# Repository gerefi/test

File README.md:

<div align="center">

<b>GPL open-source ECU</b>

</div>

# gerEFI

See [gcc_version_check.c](https://github.com/gerefi/gerefi/blob/master/firmware/gcc_version_check.c) for recommended version of GCC.

Current binaries are always available on our [build server](http://gerefi.com/build_server/)

[shop.gerEFI.com](https://www.shop.gerefi.com/)

# Cloning the repository
`git clone https://github.com/gerefi/gerefi.git`
Important note - we now use submodules:

`git submodule update --init`

# What do we have here?
 * [Firmware](/firmware) Source code for open source engine control unit for stm32 chips incuding [implementation overview](https://github.com/gerefi/gerefi/blob/master/firmware/readme.md)
 * [Hardware](/hardware) KiCAD files for our older PCBs
 * [gerEFI console](/java_console) gerEFI own native tuning software
 * [Simulator](/simulator) win32 or posix version of firmware allows to explore without any hardware
 * [Unit Tests](/unit_tests) Unit tests of firmware pieces
 * [Misc tools](/java_tools) Misc development utilities
 * [Software Development process](misc/SoftwareDevelopmentProcess.md)

# External Links

 * [Forum](http://gerefi.com/forum)
 * [Documentation](https://github.com/gerefi/gerefi/wiki)
 * [Doxygen documentation](http://gerefi.com/docs/html)
 * [General source code Q&A](http://gerefi.com/forum/viewtopic.php?f=5&t=10)
 * [Facebook](https://www.facebook.com/gerEfiECU)
 * [YouTube](https://www.youtube.com/user/gerefi)
 * [Patreon](https://www.patreon.com/gerefi)

# Building the Code
Check out https://gerefi.com/forum/viewtopic.php?f=5&t=9

# Release Notes

See [the changelog](firmware/CHANGELOG.md)

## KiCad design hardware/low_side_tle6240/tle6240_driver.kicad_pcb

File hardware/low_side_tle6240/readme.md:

TLE6240GP module - integrated low side switch

https://youtu.be/H8Tr4kTaYAI

https://gerefi.com/forum/viewtopic.php?f=4&t=398

All 16 channels can be controlled via the serial interface (SPI). In addition to the serial control it is possible to
control channel 1 to 4 and 9 to 12 direct in parallel with a separate input pin.

https://github.com/gerefi/gerefi_documentation/blob/master/oem_docs/Infineon/Infineon-TLE6240GP-DS-v03_03-en.pdf

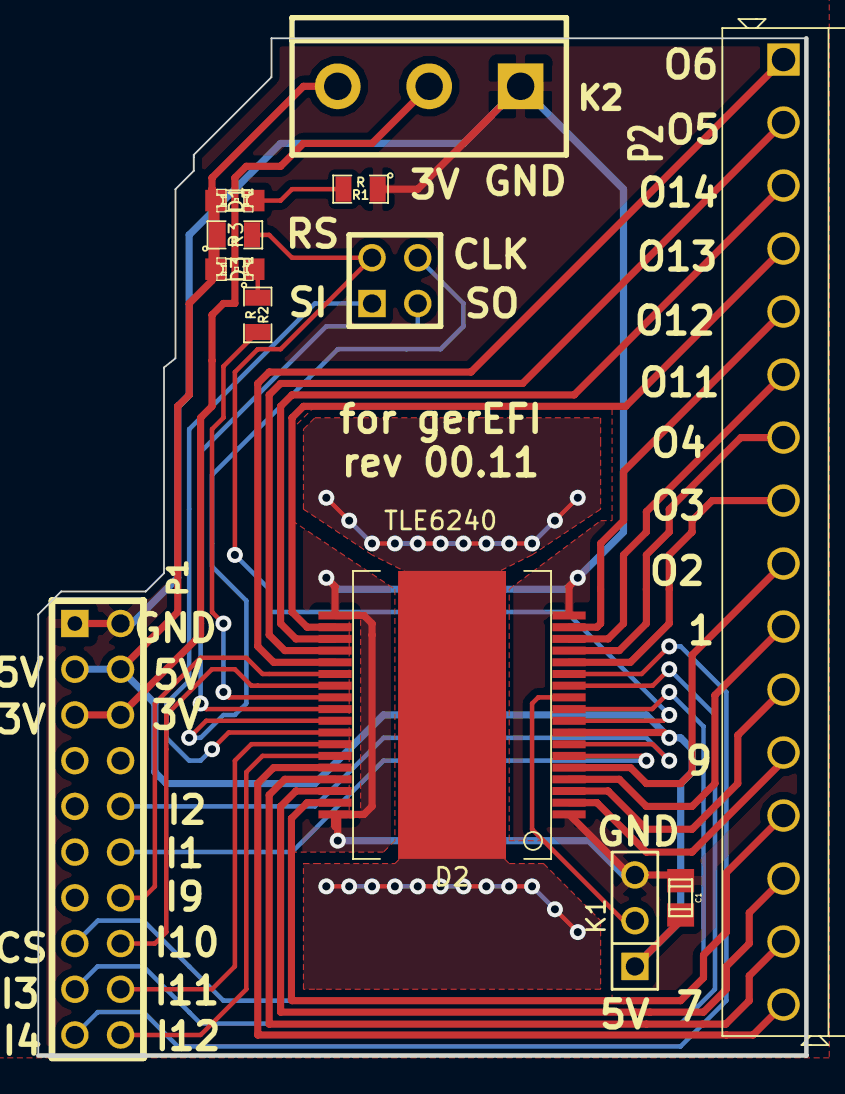
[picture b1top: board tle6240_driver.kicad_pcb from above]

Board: 2 copper layers, 42.7 x 56.5 mm, 12 parts (0 on the bottom side), 36 nets.

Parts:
C1: C; c_0805
D1, D3: LED; LED-0805
D2: TLE6240; PG-DSO-36
K1: JUMPER3; PIN_ARRAY_3X1
K2: CONN_3; bornier3
P1: CONN_10X2; PIN_ARRAY_10X2
P2: CONN_16; SIL-16_3.5MM
P3: CONN_2X2; PIN_ARRAY_2X2
R1, R2, R3: R; SM0805

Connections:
+5V: C1.1, D1.1, D2.8, D3.1, K1.1, K2.3, P1.3, P1.4, R3.1
/+3.3V: K2.2, P1.5, P1.6
/CS: D2.10, P1.15
/Fault: D2.26, R2.2
/IN1: D2.6, P1.12
/IN2: D2.7, P1.10
/IN3: D2.12, P1.17
/IN4: D2.13, P1.19
/IN9: D2.24, P1.14
/IN10: D2.25, P1.16
/IN11: D2.30, P1.18
/IN12: D2.31, P1.20
/OUT1: D2.4, P2.10
/OUT2: D2.5, P2.9
/OUT3: D2.14, P2.8
/OUT4: D2.15, P2.7
/OUT5: D2.22, P2.2
/OUT6: D2.23, P2.1
/OUT7: D2.32, P2.16
/OUT8: D2.33, P2.15
/OUT9: D2.2, P2.12
/OUT10: D2.3, P2.11
/OUT11: D2.16, P2.6
/OUT12: D2.17, P2.5
/OUT13: D2.20, P2.4
/OUT14: D2.21, P2.3
/OUT15: D2.34, P2.14
/OUT16: D2.35, P2.13
/PRG: D2.11, K1.2
/Reset: D2.9, P3.2, R3.2
/SCLK: D2.28, P3.4
/SI: D2.29, P3.1
/SO: D2.27, P3.3
GND: C1.2, D2.1, D2.18, D2.19, D2.36, K1.3, K2.1, P1.1, P1.2, R1.1
unnamed: D3.2, R2.1
unnamed: D1.2, R1.2

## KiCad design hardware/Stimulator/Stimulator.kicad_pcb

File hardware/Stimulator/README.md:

Stimulator
==========

Gerefi Stimulator

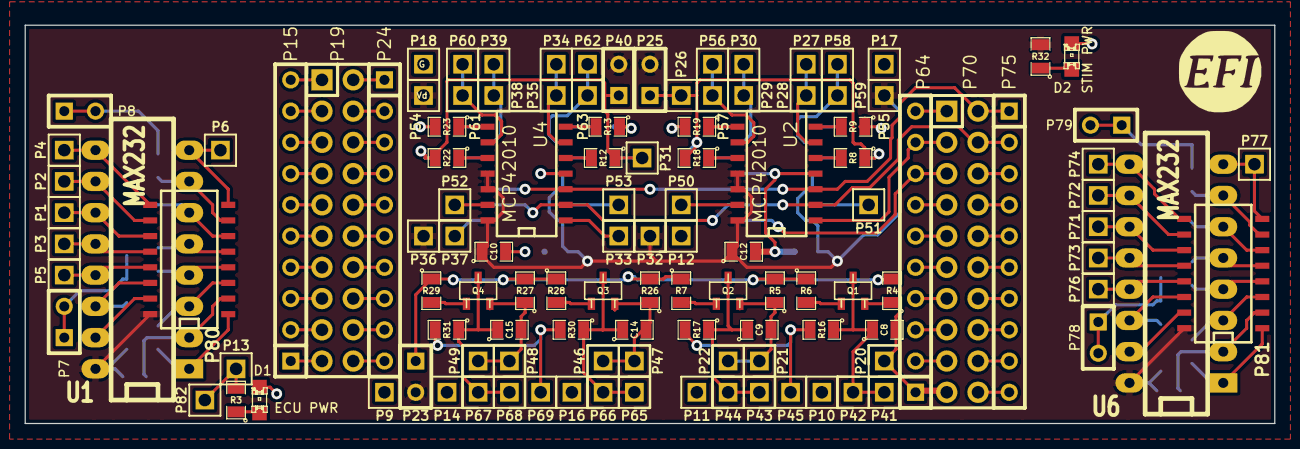
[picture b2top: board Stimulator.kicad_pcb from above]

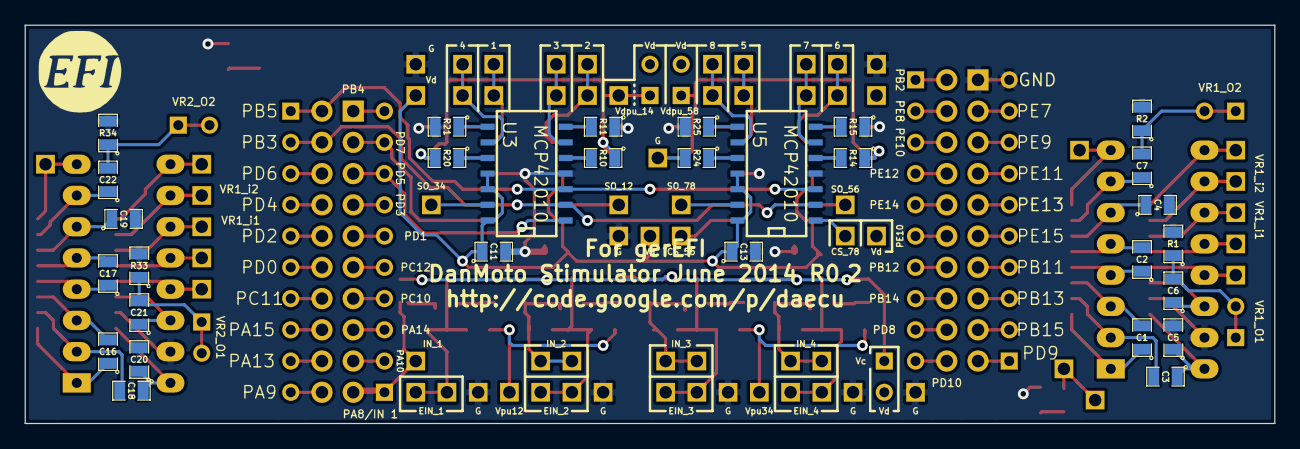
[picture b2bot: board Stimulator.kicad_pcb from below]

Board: 2 copper layers, 101.6 x 32.4 mm, 150 parts (30 on the bottom side), 122 nets.

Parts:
C1, C2, C3, C4, C5, C6, C7, C16, C17, C18, C19, C20, C21, C22: 1uF; SM0805
C8, C9, C14, C15: 100 pF; SM0805
C10, C11, C12, C13: 0.1uF; SM0805
D1: ECU PWR; LED-0805
D2: STIM PWR; LED-0805
P1, P2, P3, P4, P5, P6, P9, P10, P11, P12, P13, P14, P16, P17, P18, P20, P21, P22, P26, P27, P28, P29, P30, P31, P32, P33, P34, P35, P36, P37, P38, P39, P41, P42, P43, P44, P45, P46, P47, P48, P49, P50, P51, P52, P53, P54, P55, P56, P57, P58, P59, P60, P61, P62, P63, P65, P66, P67, P68, P69, P71, P72, P73, P74, P76, P77, P82: CONN_1; PIN_ARRAY_1
P7, P8, P23, P25, P40, P78, P79: TEST; SIL-2
P15, P24, P64, P75: CONN_10; SIL-10
P19, P70: CONN_10X2; Pin_Header_Straight_2x10
P80, P81: DIL16; SO16N
Q1, Q2, Q3, Q4: 2N7002; sot23
R1, R2, R4, R5, R6, R7, R16, R17, R26, R27, R28, R29, R30, R31, R33, R34: 10k; SM0805
R3, R32: 700R; SM0805
R8, R9, R10, R11, R12, R13, R14, R15, R18, R19, R20, R21, R22, R23, R24, R25: 0; SM0805
U1, U6: MAX232; DIP-16__300_ELL
U2, U3, U4, U5: MCP42010; SO14N

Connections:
/CS_12: P64.9, P70.3, U2.1
/CS_34: P64.8, P70.5, U3.1
/CS_56: P33.1, U4.1
/CS_78: P37.1, U5.1
/EIN_1: C8.1, P41.1, P42.1, Q1.2, R16.1
/EIN_2: C9.1, P43.1, P44.1, Q2.2, R17.1
/EIN_3: C14.1, P65.1, P66.1, Q3.2, R30.1
/EIN_4: C15.1, P67.1, P68.1, Q4.2, R31.1
/IN_1: C8.2, P20.1, P64.1, P70.19, Q1.3, R4.1
/IN_2: C9.2, P21.1, P22.1, Q2.3, R5.1
/IN_3: C14.2, P46.1, P47.1, Q3.3, R26.1
/IN_4: C15.2, P48.1, P49.1, Q4.3, R27.1
/MISO: P64.10, P70.1
/MOSI: P70.2, P75.1, U2.3, U3.3, U4.3, U5.3
/OUT1: P27.1, P28.1, U2.6
/OUT2: P56.1, P57.1, U2.9
/OUT3: P29.1, P30.1, U3.6
/OUT4: P58.1, P59.1, U3.9
/OUT5: P34.1, P35.1, U4.6
/OUT6: P60.1, P61.1, U4.9
/OUT7: P38.1, P39.1, U5.6
/OUT8: P62.1, P63.1, U5.9
/SCK: P70.4, P75.2, U2.2, U3.2, U4.2, U5.2
/U1-01: C1.1, P80.1, U1.1
/U1-02: C3.2, P80.2, U1.2
/U1-03: C1.2, P80.3, U1.3
/U1-04: C2.1, P80.4, U1.4
/U1-05: C2.2, P80.5, U1.5
/U1-06: C4.1, P80.6, U1.6
/U1-07: C7.1, P80.7, U1.7
/U1-08: P6.1, P80.8, U1.8
/U1-09: P4.1, P80.9, U1.9
/U1-12: P3.1, P80.12, U1.12
/U1-13: P5.1, P80.13, U1.13
/U1-14: C6.1, P80.14, U1.14
/U6-01: C16.1, P81.1, U6.1
/U6-02: C18.2, P81.2, U6.2
/U6-03: C16.2, P81.3, U6.3
/U6-04: C17.1, P81.4, U6.4
/U6-05: C17.2, P81.5, U6.5
/U6-06: C19.1, P81.6, U6.6
/U6-07: C22.1, P81.7, U6.7
/U6-08: P77.1, P81.8, U6.8
/U6-09: P74.1, P81.9, U6.9
/U6-12: P73.1, P81.12, U6.12
/U6-13: P76.1, P81.13, U6.13
/U6-14: C21.1, P81.14, U6.14
/VR1-O1: C6.2, P7.1, P7.2, R1.1
/VR1-O2: C7.2, P8.1, P8.2, R2.1
/VR1_i1: P1.1, P80.11, U1.11
/VR1_i2: P2.1, P80.10, U1.10
/VR2-O1: C21.2, P78.1, P78.2, R33.1
/VR2-O2: C22.2, P79.1, P79.2, R34.1
/VR2_i1: P71.1, P81.11, U6.11
/VR2_i2: P72.1, P81.10, U6.10
/Vc: P23.1, R4.2, R5.2, R6.1, R7.1, R26.2, R27.2, R28.1, R29.1
/Vd: C3.1, C5.1, C10.1, C11.1, C12.1, C13.1, C18.1, C20.1, P23.2, P25.2, P32.1, P36.1, P40.2, P54.1, P55.1, P80.16, P81.16, R32.2, U1.16, U2.11, U2.12, U2.14, U3.11, U3.12, U3.14, U4.11, U4.12, U4.14, U5.11, U5.12, U5.14, U6.16
/Vdpu_14: P25.1, P26.1, R8.1, R10.1, R18.2, R20.2
/Vdpu_58: P31.1, P40.1, R12.1, R14.1, R22.2, R24.2
/Vipu12: P45.1, R16.2, R17.2
/Vipu34: P69.1, R30.2, R31.2
GND: C4.2, C5.2, C10.2, C11.2, C12.2, C13.2, C19.2, C20.2, D1.2, D2.2, P9.1, P10.1, P11.1, P12.1, P14.1, P15.10, P16.1, P17.1, P18.1, P19.1, P80.15, P81.15, R1.2, R2.2, R9.1, R11.1, R13.1, R15.1, R19.2, R21.2, R23.2, R25.2, R33.2, R34.2, U1.15, U2.4, U3.4, U4.4, U5.4, U6.15
unnamed: P70.6, P75.3
unnamed: P70.20, P75.10
unnamed: P64.2, P70.17
unnamed: P64.3, P70.15
unnamed: P64.4, P70.13
unnamed: P64.5, P70.11
unnamed: P64.6, P70.9
unnamed: P64.7, P70.7
unnamed: P70.18, P75.9
unnamed: P70.8, P75.4
unnamed: P70.10, P75.5
unnamed: P70.12, P75.6
unnamed: P70.14, P75.7
unnamed: P70.16, P75.8
unnamed: P15.5, P19.11
unnamed: P19.4, P24.2
unnamed: P19.6, P24.3
unnamed: P19.8, P24.4
unnamed: P19.10, P24.5
unnamed: P19.12, P24.6
unnamed: P19.14, P24.7
unnamed: P19.16, P24.8
unnamed: P19.18, P24.9
unnamed: P19.20, P24.10
unnamed: P15.1, P19.19
unnamed: P15.2, P19.17
unnamed: P15.3, P19.15
unnamed: P15.4, P19.13
unnamed: P15.6, P19.9
unnamed: P15.7, P19.7
unnamed: P15.8, P19.5
unnamed: P15.9, P19.3
unnamed: P19.2, P24.1
unnamed: R14.2, U5.5
unnamed: R15.2, U5.7
unnamed: R25.1, U5.8
unnamed: R24.1, U5.10
unnamed: P50.1, U2.13
unnamed: P52.1, U4.13
unnamed: P51.1, U3.13
unnamed: P53.1, U5.13
unnamed: P13.1, P82.1, R3.2
unnamed: D2.1, R32.1
unnamed: D1.1, R3.1
unnamed: R8.2, U2.5
unnamed: R9.2, U2.7
unnamed: R19.1, U2.8
unnamed: R18.1, U2.10
unnamed: R10.2, U3.5
unnamed: Q3.1, R28.2
unnamed: Q2.1, R7.2
unnamed: Q4.1, R29.2
unnamed: R11.2, U3.7
unnamed: R21.1, U3.8
unnamed: R20.1, U3.10
unnamed: R12.2, U4.5
unnamed: R13.2, U4.7
unnamed: R23.1, U4.8
unnamed: R22.1, U4.10
unnamed: Q1.1, R6.2

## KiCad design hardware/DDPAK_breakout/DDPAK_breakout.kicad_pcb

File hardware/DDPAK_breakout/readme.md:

https://gerefi.com/forum/viewtopic.php?f=4&t=286

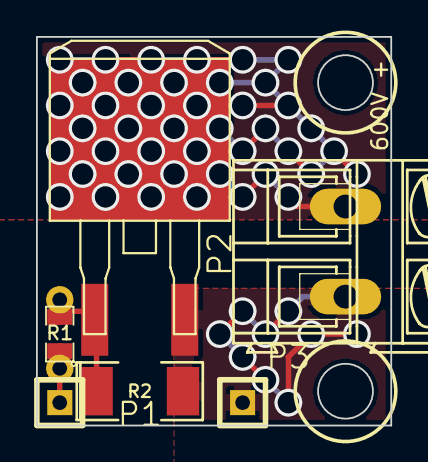
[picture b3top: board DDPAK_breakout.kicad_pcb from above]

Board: 2 copper layers, 19.7 x 21.6 mm, 6 parts (0 on the bottom side), 4 nets.

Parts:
P1, P3: CONN_1; SIL-1
P2: CONN_2; AK300-2
Q1: IRGS14C40L; m-pad-2.1-TO-263AB
R1: 1K; SM0805_jumper
R2: 100K; SM2010

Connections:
/GND: P2.2, P3.1, Q1.3, R2.2
/HV: P2.1, Q1.2
/SIG: P1.1, R1.1
/SIG2: Q1.1, R1.2, R2.1

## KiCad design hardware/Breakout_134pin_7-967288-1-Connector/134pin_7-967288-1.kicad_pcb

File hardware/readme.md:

# Connectors
Some vehicle-specific connector boards are also pretty nice if you want to keep original harness intact

See [Connectors wiki page](http://gerefi.com/wiki/index.php?title=Hardware:OEM_connectors)
todo: move Connectors wiki page content into git

* [35 pin](Breakout_35pin_MX7-C-35PL-C11-connector) Mazda TCU
* [38 pin](Breakout_38pin_NGC-connector) Chrysler NGC connector
* [48 pin](Breakout_48pin_174917-Connector) Mazda Miata NA6
* [52 pin](Breakout_52pin_172319-1-Connector) Mitsubishi Galant VR4
* [55 pin](Breakout_55pin_963063-15-Connector) TE Lada
* [55 pin](breakout_55pin-motronic-Connector) Motronic 1.5.x BMW/GM
* [60 pin](Breakout_60pin_EEC-IV-Connector) Ford EEC-IV
* [64 pin](Breakout_64pin_176122-6-Connector) Mazda Miata NA NB1, Honda Civic
* [68 pin](Breakout_68pin_966595-1_and_963356-1-Connector) Volkswagen Audi VAG
* [72 pin](Breakout_72pin_1123038-2-Connector) Mazda Miata NB2
* [88 pin](Breakout_88pin_VAG-Connector) Volkswagen Audi VAG
* [121 pin](Breakout_121pin_368255-2-Connector) Volkswagen Audi VAG
* [134 pin](Breakout_134pin_7-967288-1-Connector) BWM
* [154 pin](Breakout_154pin_284617-1-Connector) Volkswagen Audi VAG

# Modules
* [stm32 Brain board 48pin](mini48-stm32)
* [stm32 Brain board 100pin](brain_board)
* [stm32 Brain board 176pin](brain_board_176-pin)
* [CAN module](can_board) CAN using SN65HVD230
* [VR module](VR_Board) Variable Reluctance conditioner board VR MAX9926
* [Wideband module](CJ125_board) CJ125 Bosch Wideband board
* [VND5E025AKTR](PowerSSO-24_breakout) double channel high-side driver with analog current sense (used on Dodge Neon 2003 test mule)
* [BTS21400](DDPAK_breakout) ignition coil IGBT driver (used on Dodge Neon 2003 test mule)
* [TLE6240 module](low_side_tle6240) integrated low side switch (fabricated, not tested)
* [TLE6244 module](Breakout_TLE6244) integrated low side switch (never actually fabricated)
* [TLE8810ED module](https://github.com/gerefi/hw_modular/tree/master/TLE8110ED_breakout_board) integrated low side switch
* [MC33816](Common_Rail_MC33816) common rail driver - gerEFI has working GDI*
* [LM1949]([Low-Z_LM1949](https://github.com/gerefi/hw_legacy/tree/master/Low-Z_LM1949)) low impedance injector driver (never actually fabricated)

New modules are being added to https://github.com/gerefi/hw_modular

Some stuff we have given up on completely is located at https://github.com/gerefi/hw_legacy

Above mentioned modules are known to work unless stated otherwise

### More gerEFI hardware

See https://github.com/gerefi/gerefi/wiki/Hardware

# Frankenso
Frankenso has moved to https://github.com/gerefi/gerefi-hardware/tree/main/classic-designs

# More info

 [Interactive Html Boms](https://gerefi.com/docs/ibom/)

See [Hardware status forum thread](http://gerefi.com/forum/viewtopic.php?f=4&t=260)
todo: move hardware status content into git

# Important note
gerEFI is currently transitioning from KiCAD 4 to KiCAD 5.

# Important note

Depends on libraries from https://github.com/gerefi/kicad-libraries

If you download complete repo do not forget to download libraries. If you git clone be sure to also

`git submodule update --init`

`git submodule update --init`

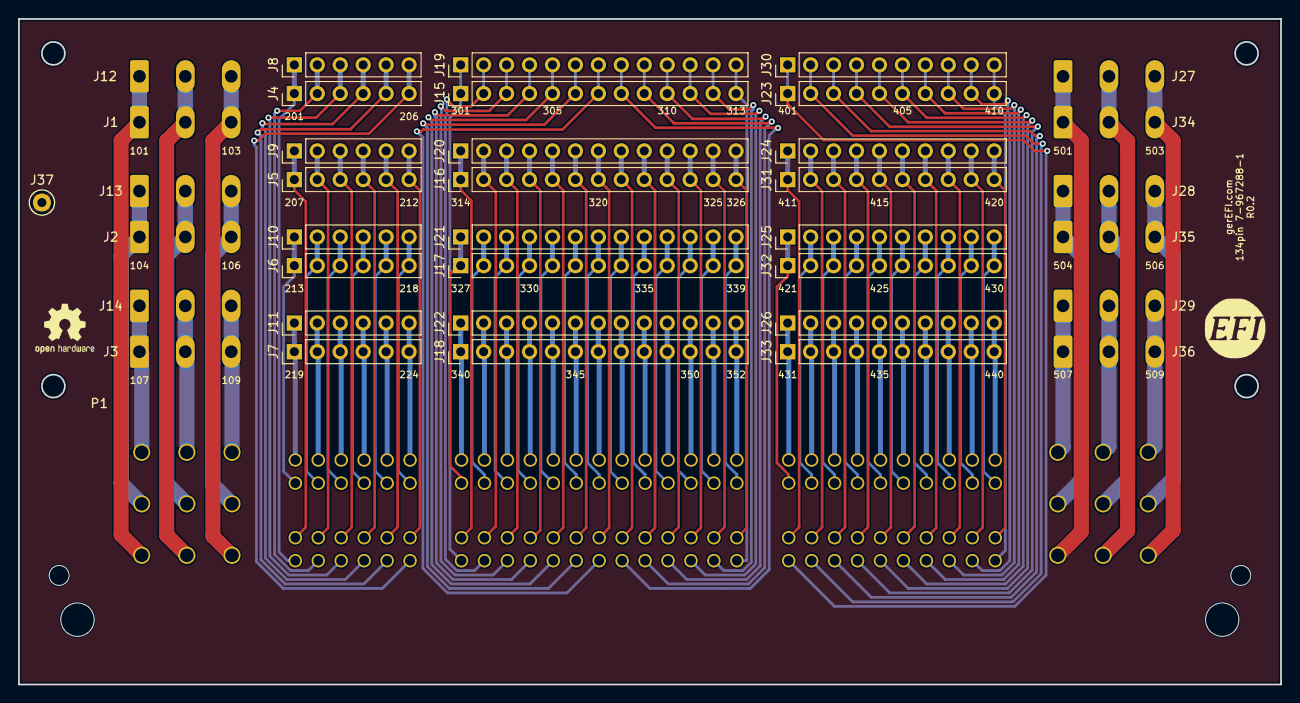
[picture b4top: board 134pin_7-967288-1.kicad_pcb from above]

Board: 2 copper layers, 139.7 x 73.7 mm, 40 parts (0 on the bottom side), 134 nets.

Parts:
J1, J2, J3, J12, J13, J14, J27, J28, J29, J34, J35, J36: Conn_01x03; PhoenixContact_MSTBA_2,5_3-G-5,08_1x03_P5.08mm_Horizontal
J4, J5, J6, J7, J8, J9, J10, J11: Conn_01x06; PinHeader_1x06_P2.54mm_Vertical
J15, J16, J17, J18, J19, J20, J21, J22: Conn_01x13; PinHeader_1x13_P2.54mm_Vertical
J23, J24, J25, J26, J30, J31, J32, J33: Conn_01x10; PinHeader_1x10_P2.54mm_Vertical
J37: Conn_01x01; TestPoint_Keystone_5000-5004_Miniature
LOGO1: DNP; LOGO
LOGO2: DNP; OSHW-Logo2_7.3x6mm_SilkScreen
P1: 134pin_7-967288-1_KC5; 7-967288-1_134-pin-connector

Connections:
/101: J1.1, J12.1, P1.101
/103: J1.3, J12.3, P1.103
/104: J2.1, J13.1, P1.104
/106: J2.3, J13.3, P1.106
/107: J3.1, J14.1, P1.107
/109: J3.3, J14.3, P1.109
/201: J4.1, J8.1, P1.201
/206: J4.6, J8.6, P1.206
/207: J5.1, J9.1, P1.207
/212: J5.6, J9.6, P1.212
/213: J6.1, J10.1, P1.213
/218: J6.6, J10.6, P1.218
/219: J7.1, J11.1, P1.219
/224: J7.6, J11.6, P1.224
/301: J15.1, J19.1, P1.301
/305: J15.5, J19.5, P1.305
/310: J15.10, J19.10, P1.310
/313: J15.13, J19.13, P1.313
/314: J16.1, J20.1, P1.314
/315: J16.2, J20.2, P1.315
/320: J16.7, J20.7, P1.320
/325: J16.12, J20.12, P1.325
/326: J16.13, J20.13, P1.326
/327: J17.1, J21.1, P1.327
/330: J17.4, J21.4, P1.330
/335: J17.9, J21.9, P1.335
/339: J17.13, J21.13, P1.339
/340: J18.1, J22.1, P1.340
/345: J18.6, J22.6, P1.345
/350: J18.11, J22.11, P1.350
/352: J18.13, J22.13, P1.352
/401: J23.1, J30.1, P1.401
/405: J23.5, J30.5, P1.405
/410: J23.10, J30.10, P1.410
/411: J24.1, J31.1, P1.411
/415: J24.5, J31.5, P1.415
/420: J24.10, J31.10, P1.420
/421: J25.1, J32.1, P1.421
/425: J25.5, J32.5, P1.425
/430: J25.10, J32.10, P1.430
/431: J26.1, J33.1, P1.431
/435: J26.5, J33.5, P1.435
/440: J26.10, J33.10, P1.440
/501: J27.1, J34.1, P1.501
/503: J27.3, J34.3, P1.503
/504: J28.1, J35.1, P1.504
/506: J28.3, J35.3, P1.506
/507: J29.1, J36.1, P1.507
/509: J29.3, J36.3, P1.509
unnamed: J1.2, J12.2, P1.102
unnamed: J4.2, J8.2, P1.202
unnamed: J4.3, J8.3, P1.203
unnamed: J4.4, J8.4, P1.204
unnamed: J4.5, J8.5, P1.205
unnamed: J5.2, J9.2, P1.208
unnamed: J5.3, J9.3, P1.209
unnamed: J5.4, J9.4, P1.210
unnamed: J5.5, J9.5, P1.211
unnamed: J6.2, J10.2, P1.214
unnamed: J6.3, J10.3, P1.215
unnamed: J6.4, J10.4, P1.216
unnamed: J6.5, J10.5, P1.217
unnamed: J7.2, J11.2, P1.220
unnamed: J7.3, J11.3, P1.221
unnamed: J7.4, J11.4, P1.222
unnamed: J7.5, J11.5, P1.223
unnamed: J2.2, J13.2, P1.105
unnamed: J3.2, J14.2, P1.108
unnamed: J15.2, J19.2, P1.302
unnamed: J15.3, J19.3, P1.303
unnamed: J15.4, J19.4, P1.304
unnamed: J15.6, J19.6, P1.306
unnamed: J15.7, J19.7, P1.307
unnamed: J15.8, J19.8, P1.308
unnamed: J15.9, J19.9, P1.309
unnamed: J15.11, J19.11, P1.311
unnamed: J15.12, J19.12, P1.312
unnamed: J16.3, J20.3, P1.316
unnamed: J16.4, J20.4, P1.317
unnamed: J16.5, J20.5, P1.318
unnamed: J16.6, J20.6, P1.319
unnamed: J16.8, J20.8, P1.321
unnamed: J16.9, J20.9, P1.322
unnamed: J16.10, J20.10, P1.323
unnamed: J16.11, J20.11, P1.324
unnamed: J17.2, J21.2, P1.328
unnamed: J17.3, J21.3, P1.329
unnamed: J17.5, J21.5, P1.331
unnamed: J17.6, J21.6, P1.332
unnamed: J17.7, J21.7, P1.333
unnamed: J17.8, J21.8, P1.334
unnamed: J17.10, J21.10, P1.336
unnamed: J17.11, J21.11, P1.337
unnamed: J17.12, J21.12, P1.338
unnamed: J18.2, J22.2, P1.341
unnamed: J18.3, J22.3, P1.342
unnamed: J18.4, J22.4, P1.343
unnamed: J18.5, J22.5, P1.344
unnamed: J18.7, J22.7, P1.346
unnamed: J18.8, J22.8, P1.347
unnamed: J18.9, J22.9, P1.348
unnamed: J18.10, J22.10, P1.349
unnamed: J18.12, J22.12, P1.351
unnamed: J23.2, J30.2, P1.402
unnamed: J23.3, J30.3, P1.403
unnamed: J23.4, J30.4, P1.404
unnamed: J23.6, J30.6, P1.406
unnamed: J23.7, J30.7, P1.407
unnamed: J23.8, J30.8, P1.408
unnamed: J23.9, J30.9, P1.409
unnamed: J24.2, J31.2, P1.412
unnamed: J24.3, J31.3, P1.413
unnamed: J24.4, J31.4, P1.414
unnamed: J24.6, J31.6, P1.416
unnamed: J24.7, J31.7, P1.417
unnamed: J24.8, J31.8, P1.418
unnamed: J24.9, J31.9, P1.419
unnamed: J25.2, J32.2, P1.422
unnamed: J25.3, J32.3, P1.423
unnamed: J25.4, J32.4, P1.424
unnamed: J25.6, J32.6, P1.426
unnamed: J25.7, J32.7, P1.427
unnamed: J25.8, J32.8, P1.428
unnamed: J25.9, J32.9, P1.429
unnamed: J26.2, J33.2, P1.432
unnamed: J26.3, J33.3, P1.433
unnamed: J26.4, J33.4, P1.434
unnamed: J26.6, J33.6, P1.436
unnamed: J26.7, J33.7, P1.437
unnamed: J26.8, J33.8, P1.438
unnamed: J26.9, J33.9, P1.439
unnamed: J27.2, J34.2, P1.502
unnamed: J28.2, J35.2, P1.505
unnamed: J29.2, J36.2, P1.508

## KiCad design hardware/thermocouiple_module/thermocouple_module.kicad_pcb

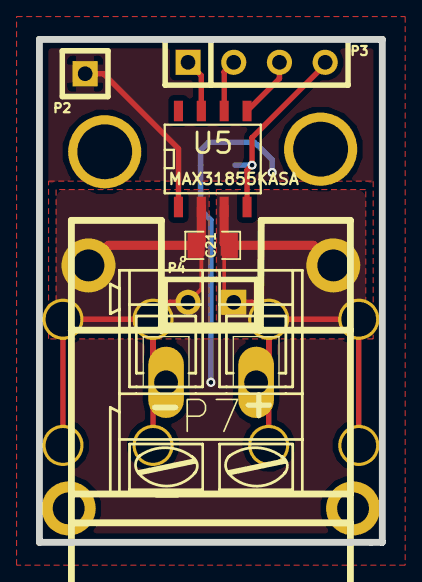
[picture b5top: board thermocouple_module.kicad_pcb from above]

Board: 2 copper layers, 19.0 x 27.9 mm, 12 parts (1 on the bottom side), 7 nets.

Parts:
C8: 100nF; SM0805-SM0603
C21: 10nF; SM0805-SM0603
P1: CONN_2; tcpl_PCC-SMP
P2: CONN_1; SIL-1
P3: CONN_4; SIL-4
P4: CONN_2; SIL-2
P5, P6: CONN_1; SCREW_TERM_534-7693
P7: CONN_2; AK300-2
U5: MAX31855KASA; SO8E
V801, V802: VIA; 1pin

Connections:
3.3v: C8.1, P3.4, U5.4
//CS: P3.2, U5.6
/MISO: P3.1, U5.7
/SCK: P3.3, U5.5
/TCPL+: C21.2, P1.2, P4.1, P6.1, P7.1, U5.3
/TCPL-: C21.1, P1.1, P4.2, P5.1, P7.2, U5.2
GND: C8.2, P2.1, U5.1

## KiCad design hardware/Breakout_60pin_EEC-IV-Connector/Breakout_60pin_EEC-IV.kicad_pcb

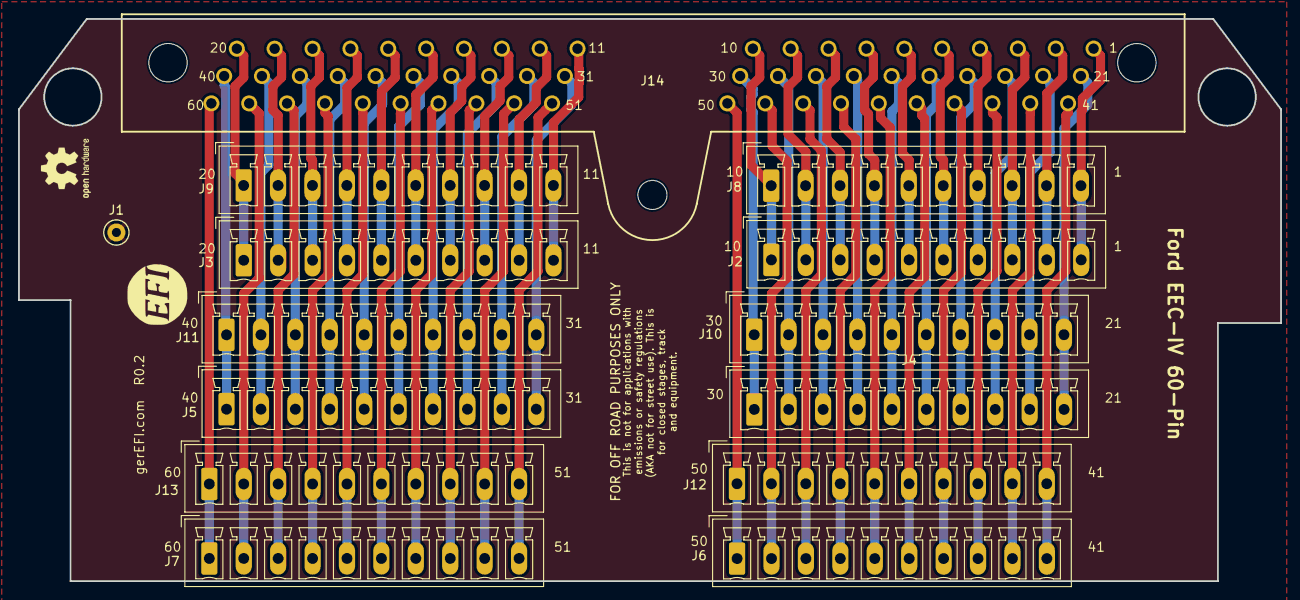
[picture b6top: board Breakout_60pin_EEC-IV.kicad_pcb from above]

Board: 2 copper layers, 139.7 x 62.2 mm, 17 parts (0 on the bottom side), 60 nets.

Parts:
G1: Disclaimer; Off_Road_Disclaimer
G2: LOGO
J1: Conn_01x01; TestPoint_Keystone_5000-5004_Miniature
J2, J3, J4, J5, J6, J7, J8, J9, J10, J11, J12, J13: Conn_01x10; PhoenixContact_MCV_1,5_10-G-3.81_1x10_P3.81mm_Vertical
J14: EEC-IV; eeciv
LOGO1: DNP; OSHW-Logo2_7.3x6mm_SilkScreen

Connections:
/1: J2.10, J8.10, J14.1
/5: J2.6, J8.6, J14.5
/10: J2.1, J8.1, J14.10
/11: J3.10, J9.10, J14.11
/15: J3.6, J9.6, J14.15
/25: J4.6, J10.6, J14.25
/30: J4.1, J10.1, J14.30
/31: J5.10, J11.10, J14.31
/35: J5.6, J11.6, J14.35
/40: J5.1, J11.1, J14.40
/41: J6.10, J12.10, J14.41
/45: J6.6, J12.6, J14.45
/50: J6.1, J12.1, J14.50
/53: J7.8, J13.8, J14.53
/54: J7.7, J13.7, J14.54
/55: J7.6, J13.6, J14.55
/60: J7.1, J13.1, J14.60
/420: J3.1, J9.1, J14.20
/421: J4.10, J10.10, J14.21
unnamed: J4.2, J10.2, J14.29
unnamed: J4.3, J10.3, J14.28
unnamed: J4.4, J10.4, J14.27
unnamed: J4.5, J10.5, J14.26
unnamed: J4.7, J10.7, J14.24
unnamed: J4.8, J10.8, J14.23
unnamed: J4.9, J10.9, J14.22
unnamed: J5.2, J11.2, J14.39
unnamed: J5.3, J11.3, J14.38
unnamed: J5.4, J11.4, J14.37
unnamed: J5.5, J11.5, J14.36
unnamed: J5.7, J11.7, J14.34
unnamed: J5.8, J11.8, J14.33
unnamed: J5.9, J11.9, J14.32
unnamed: J6.2, J12.2, J14.49
unnamed: J6.3, J12.3, J14.48
unnamed: J6.4, J12.4, J14.47
unnamed: J6.5, J12.5, J14.46
unnamed: J6.7, J12.7, J14.44
unnamed: J6.8, J12.8, J14.43
unnamed: J6.9, J12.9, J14.42
unnamed: J7.2, J13.2, J14.59
unnamed: J7.3, J13.3, J14.58
unnamed: J7.4, J13.4, J14.57
unnamed: J7.5, J13.5, J14.56
unnamed: J7.9, J13.9, J14.52
unnamed: J7.10, J13.10, J14.51
unnamed: J2.9, J8.9, J14.2
unnamed: J2.8, J8.8, J14.3
unnamed: J2.7, J8.7, J14.4
unnamed: J2.5, J8.5, J14.6
unnamed: J2.4, J8.4, J14.7
unnamed: J2.3, J8.3, J14.8
unnamed: J2.2, J8.2, J14.9
unnamed: J3.9, J9.9, J14.12
unnamed: J3.8, J9.8, J14.13
unnamed: J3.7, J9.7, J14.14
unnamed: J3.5, J9.5, J14.16
unnamed: J3.4, J9.4, J14.17
unnamed: J3.3, J9.3, J14.18
unnamed: J3.2, J9.2, J14.19

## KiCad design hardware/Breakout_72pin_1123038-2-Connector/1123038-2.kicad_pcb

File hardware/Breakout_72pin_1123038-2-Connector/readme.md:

72 pin connector Mazda Miata MX-5 NB2

# [For sale here](https://www.tindie.com/products/russian/72p-connector-bare-pcb-miata-nb2/)

[Known Issues](known_issues.txt)

[Forum thread](https://gerefi.com/forum/viewtopic.php?f=4&t=687)

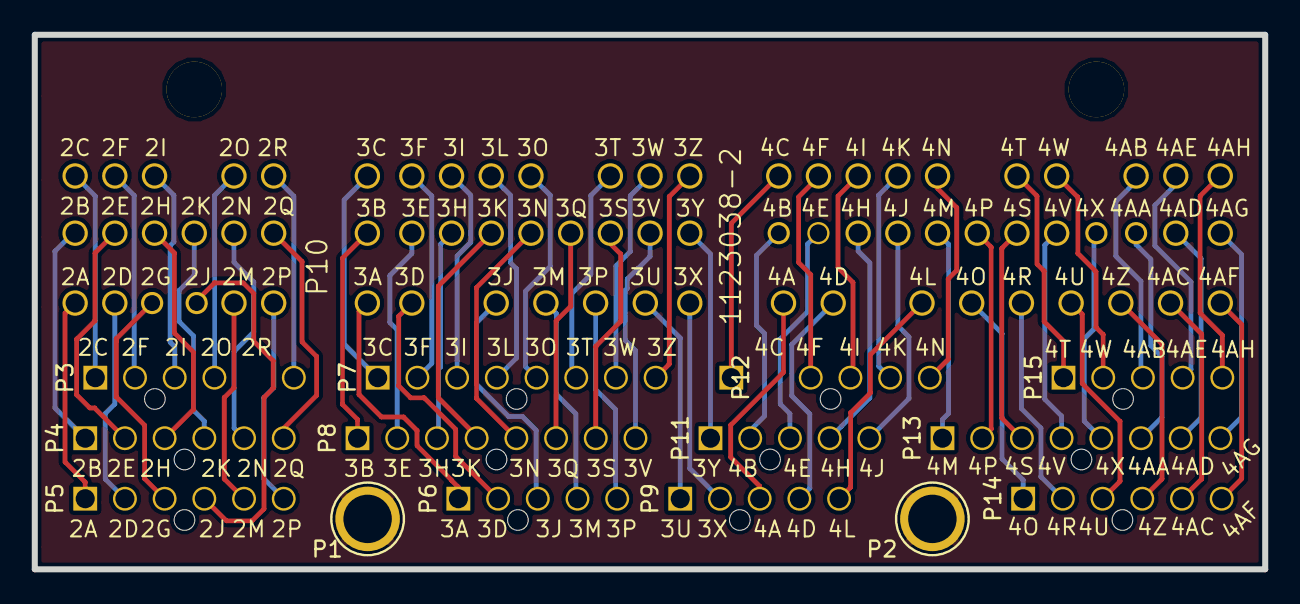
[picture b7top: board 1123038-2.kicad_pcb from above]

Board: 2 copper layers, 77.5 x 33.7 mm, 16 parts (1 on the bottom side), 73 nets.

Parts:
G1: LOGO
P1, P2: CONN_1; 1pin
P3, P6, P9, P11, P12, P15: CONN_01X05; Molex_NanoFit_1x05x2.50mm_Straight
P4, P5, P14: CONN_01X06; Molex_NanoFit_1x06x2.50mm_Straight
P7, P8, P13: CONN_01X08; Molex_NanoFit_1x08x2.50mm_Straight
P10: 1123038-2

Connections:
/2A: P5.1, P10.51
/2B: P4.1, P10.24
/2C: P3.1, P10.1
/2D: P5.2, P10.52
/2E: P4.2, P10.25
/2F: P3.2, P10.2
/2G: P5.3, P10.53
/2H: P4.3, P10.26
/2I: P3.3, P10.3
/2J: P5.4, P10.54
/2K: P4.4, P10.27
/2M: P5.5, P10.55
/2N: P4.5, P10.28
/2P: P5.6, P10.56
/2Q: P4.6, P10.29
/2R: P3.5, P10.5
/3A: P6.1, P10.57
/3B: P8.1, P10.30
/3C: P7.1, P10.6
/3D: P6.2, P10.58
/3E: P8.2, P10.31
/3F: P7.2, P10.7
/3H: P8.3, P10.32
/3I: P7.3, P10.8
/3J: P6.3, P10.59
/3K: P8.4, P10.33
/3L: P7.4, P10.9
/3M: P6.4, P10.60
/3N: P8.5, P10.34
/3O: P7.5, P10.10
/3P: P6.5, P10.61
/3Q: P8.6, P10.35
/3S: P8.7, P10.36
/3T: P7.6, P10.11
/3U: P9.1, P10.62
/3V: P8.8, P10.37
/3W: P7.7, P10.12
/3X: P9.2, P10.63
/3Y: P10.38, P11.1
/3Z: P7.8, P10.13
/4A: P9.3, P10.64
/4AA: P10.48, P13.6
/4AB: P10.21, P15.3
/4AC: P10.71, P14.5
/4AD: P10.49, P13.7
/4AE: P10.22, P15.4
/4AF: P10.72, P14.6
/4AG: P10.50, P13.8
/4AH: P10.23, P15.5
/4B: P10.39, P11.2
/4C: P10.14, P12.1
/4D: P9.4, P10.65
/4E: P10.40, P11.3
/4F: P10.15, P12.2
/4H: P10.41, P11.4
/4I: P10.16, P12.3
/4J: P10.42, P11.5
/4K: P10.17, P12.4
/4L: P9.5, P10.66
/4M: P10.43, P13.1
/4N: P10.18, P12.5
/4O: P10.67, P14.1
/4P: P10.44, P13.2
/4R: P10.68, P14.2
/4S: P10.45, P13.3
/4T: P10.19, P15.1
/4U: P10.69, P14.3
/4V: P10.46, P13.4
/4W: P10.20, P15.2
/4X: P10.47, P13.5
/4Z: P10.70, P14.4
/20: P3.4, P10.4
GND: P1.1, P2.1

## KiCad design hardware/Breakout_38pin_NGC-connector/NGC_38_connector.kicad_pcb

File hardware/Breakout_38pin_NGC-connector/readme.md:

38 pin Chrysler NGC connector

48x32mm

[3D printed case](3D_case)

https://gerefi.com/forum/viewtopic.php?f=4&t=764

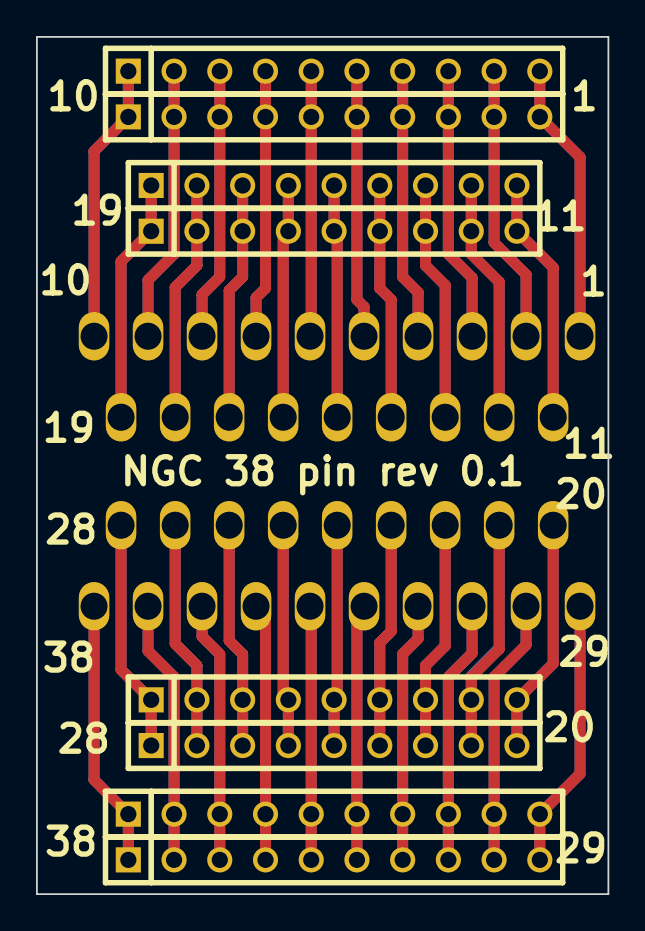
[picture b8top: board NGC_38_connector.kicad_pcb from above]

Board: 2 copper layers, 31.8 x 47.6 mm, 9 parts (0 on the bottom side), 38 nets.

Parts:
P1: DIL38; PCM_C1
P2, P4, P6, P9: CONN_10; SIL-10
P3, P5, P7, P8: CONN_9; SIL-9

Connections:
unnamed: P1.1, P2.1, P6.1
unnamed: P1.2, P2.2, P6.2
unnamed: P1.3, P2.3, P6.3
unnamed: P1.4, P2.4, P6.4
unnamed: P1.5, P2.5, P6.5
unnamed: P1.6, P2.6, P6.6
unnamed: P1.7, P2.7, P6.7
unnamed: P1.8, P2.8, P6.8
unnamed: P1.9, P2.9, P6.9
unnamed: P1.10, P2.10, P6.10
unnamed: P1.17, P3.7, P7.7
unnamed: P1.24, P5.5, P8.5
unnamed: P1.25, P5.6, P8.6
unnamed: P1.26, P5.7, P8.7
unnamed: P1.27, P5.8, P8.8
unnamed: P1.28, P5.9, P8.9
unnamed: P1.11, P3.1, P7.1
unnamed: P1.12, P3.2, P7.2
unnamed: P1.13, P3.3, P7.3
unnamed: P1.14, P3.4, P7.4
unnamed: P1.15, P3.5, P7.5
unnamed: P1.16, P3.6, P7.6
unnamed: P1.23, P5.4, P8.4
unnamed: P1.18, P3.8, P7.8
unnamed: P1.19, P3.9, P7.9
unnamed: P1.31, P4.3, P9.3
unnamed: P1.29, P4.1, P9.1
unnamed: P1.30, P4.2, P9.2
unnamed: P1.32, P4.4, P9.4
unnamed: P1.33, P4.5, P9.5
unnamed: P1.34, P4.6, P9.6
unnamed: P1.35, P4.7, P9.7
unnamed: P1.36, P4.8, P9.8
unnamed: P1.37, P4.9, P9.9
unnamed: P1.38, P4.10, P9.10
unnamed: P1.20, P5.1, P8.1
unnamed: P1.21, P5.2, P8.2
unnamed: P1.22, P5.3, P8.3

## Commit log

2025-01-15 gcc 13.2.Rel1
2025-01-15 only:gcc14
2025-01-15 only:kin
2025-01-15 Auto-generated default tune
2025-01-15 only:ts_show_jam_detection
2025-01-15 Auto-generated configs and docs
2025-01-15 only: do not trust etbJam
2025-02-13 disable stack check on cm7 as it has MPU
2025-02-13 enable stack guard on F7
2025-05-04 send blend table Y axis value so the dot moves in TS
2025-05-04 blend Y only:preparing
2025-05-13 ETB: log actual PID dt
2025-05-13 ETB: use Timer for dT measurement
    Don't believe PeriodicController
2025-05-13 ETB: allow switching dt for PID between defined and measured
2025-05-15 trigger debug? wow. only:dead
2025-05-15 fix isPinConfigurationChanged on UT case
2025-05-15 only:moving away from triggerInputDebugPins
2025-05-20 vvt3 counter only:uaefi
2025-05-22 Convert
2025-05-22 delete
2025-05-22 Change
